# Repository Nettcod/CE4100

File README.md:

# CE4100
Custom USB macro keypad for CE4100

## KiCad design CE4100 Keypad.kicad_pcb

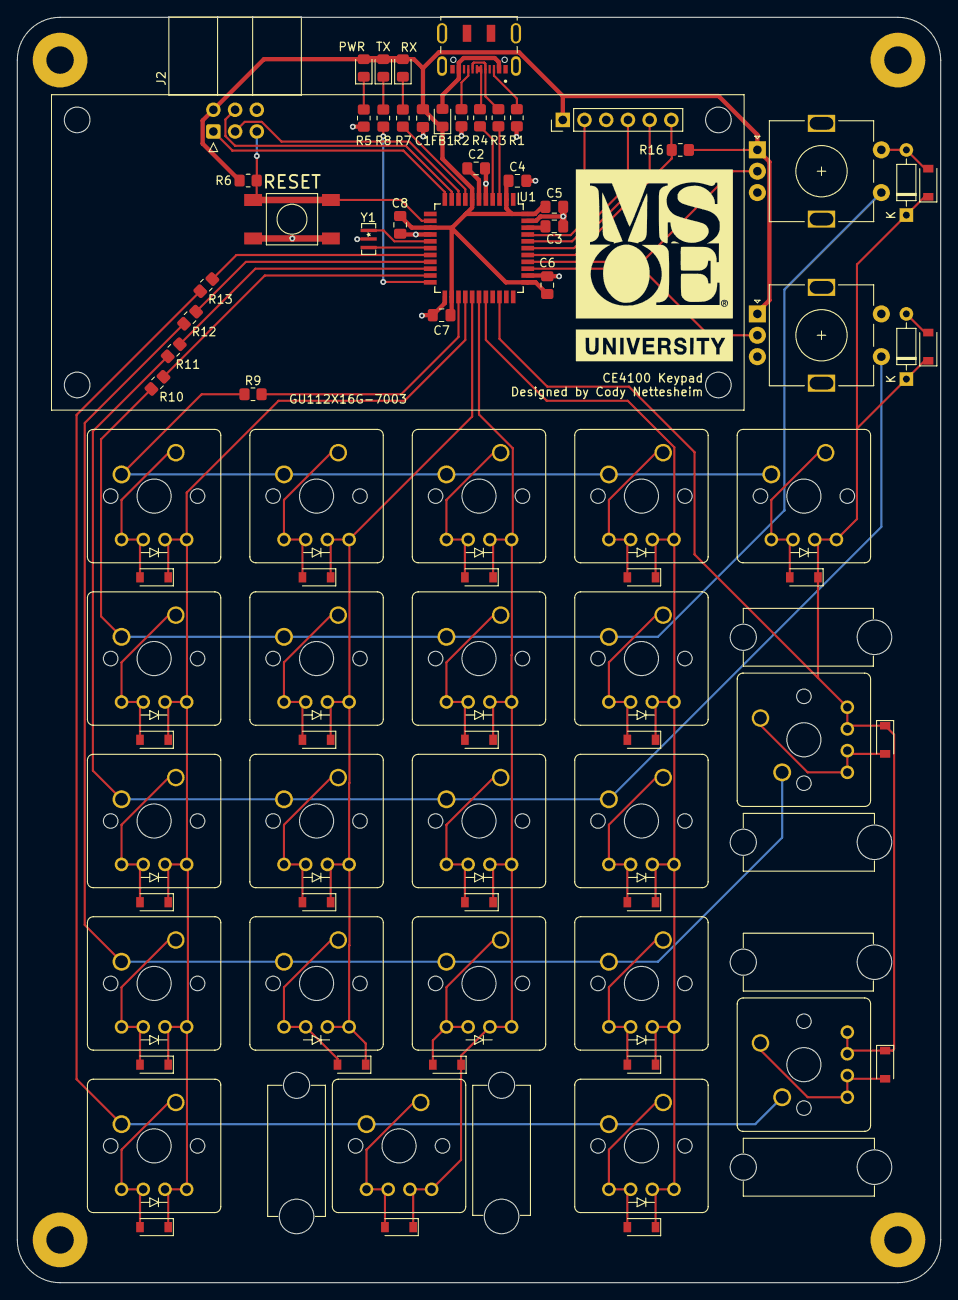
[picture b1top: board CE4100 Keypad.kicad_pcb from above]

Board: 2 copper layers, 108.0 x 148.0 mm, 87 parts (0 on the bottom side), 67 nets.

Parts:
C1: 10uF; C_0805_2012Metric_Pad1.18x1.45mm_HandSolder
C2: 1uF; C_0805_2012Metric_Pad1.18x1.45mm_HandSolder
C3, C4, C5, C6, C7, C8: 100nF; C_0805_2012Metric_Pad1.18x1.45mm_HandSolder
D1: PWR; LED_0805_2012Metric_Pad1.15x1.40mm_HandSolder
D2: RX; LED_0805_2012Metric_Pad1.15x1.40mm_HandSolder
D3: TX; LED_0805_2012Metric_Pad1.15x1.40mm_HandSolder
D4, D5, D6, D7, D8, D9, D10, D11, D12, D13, D14, D15, D16, D17, D18, D19, D20, D21, D22, D23, D24, D25, D27, D29: 1N4148_SMD; D_SOD-123
D26, D28: 1N4148_THT; D_DO-35_SOD27_P7.62mm_Horizontal
FB1: 500mA; D_0805_2012Metric_Pad1.15x1.40mm_HandSolder
G1: LOGO; MSOE
H1, H2, H3, H4: MountingHole; MountingHole_3.2mm_M3_Pad
J1: USB_C; DX07S016JA1R1500
J2: AVR-ISP; IDC-Header_2x03_P2.54mm_Horizontal
J3: GU112X16G-7003
R1, R2: 5.1K; R_0805_2012Metric_Pad1.20x1.40mm_HandSolder
R3, R4: 22; R_0805_2012Metric_Pad1.20x1.40mm_HandSolder
R5, R7, R8, R9, R10, R11, R12, R13: 330; R_0805_2012Metric_Pad1.20x1.40mm_HandSolder
R6, R16: 10K; R_0805_2012Metric_Pad1.20x1.40mm_HandSolder
SW1: RESET; FSM2JSMAA
SW2: Key_M1; Cherry_MX_Diode
SW3: Key_M2; Cherry_MX_Diode
SW4: Key_M3; Cherry_MX_Diode
SW5: Key_M4; Cherry_MX_Diode
SW6: Key_M5; Cherry_MX_Diode
SW7: Key_NumLock; Cherry_MX_Diode
SW8: Key_7; Cherry_MX_Diode
SW9: Key_4; Cherry_MX_Diode
SW10: Key_1; Cherry_MX_Diode
SW11: Key_0; Cherry_MX_Diode_1x2
SW12: Key_Slash; Cherry_MX_Diode
SW13: Key_8; Cherry_MX_Diode
SW14: Key_5; Cherry_MX_Diode
SW15: Key_2; Cherry_MX_Diode
SW16: Key_Star; Cherry_MX_Diode
SW17: Key_9; Cherry_MX_Diode
SW18: Key_6; Cherry_MX_Diode
SW19: Key_3; Cherry_MX_Diode
SW20: Key_Del; Cherry_MX_Diode
SW21: Key_Minus; Cherry_MX_Diode
SW22: Key_Plus; Cherry_MX_Diode_1x2
SW23: Key_Return; Cherry_MX_Diode_1x2
SW24, SW25: Rotary_Switch; RotaryEncoder_Alps_EC11E-Switch_Vertical_H20mm
U1: ATmega32U4; TQFP-44_10x10mm_P0.8mm
Y1: 16MHz; CSTNE_Resonator

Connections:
+5V: C1.1, C4.1, C5.1, C6.1, C7.1, C8.1, D1.2, D2.2, D3.2, FB1.1, J2.2, J3.1, R6.1, R16.1, SW24.A, SW25.A, U1.2, U1.7, U1.14, U1.24, U1.34, U1.44
/COL0: D4.1, D5.1, D6.1, D7.1, D8.1, SW2.4, SW3.4, SW4.4, SW5.4, SW6.4, U1.26
/COL1: D9.1, D10.1, D11.1, D12.1, SW7.4, SW8.4, SW9.4, SW10.4, U1.27
/COL2: D13.1, D14.1, D15.1, D16.1, D17.1, SW11.4, SW12.4, SW13.4, SW14.4, SW15.4, U1.28
/COL3: D18.1, D19.1, D20.1, D21.1, D22.1, SW16.4, SW17.4, SW18.4, SW19.4, SW20.4, U1.29
/COL4: D23.1, D24.1, D25.1, D26.1, D27.1, D28.1, D29.1, SW21.4, SW22.4, SW23.4, U1.31
/D+: R4.1, U1.4
/D-: R3.1, U1.3
/KNOB1: SW24.C, U1.37
/KNOB2: SW25.C, U1.36
/MISO: J2.1, U1.11
/MOSI: J2.4, U1.10
/ROW0: R9.2, U1.25
/ROW1: R10.2, U1.21
/ROW2: R11.2, U1.20
/ROW3: R12.2, U1.19
/ROW4: R13.2, U1.18
/SCK: J2.3, U1.9
/VFD_SBUSY: J3.4, U1.40
/VFD_SCK: J3.5, U1.39
/VFD_SIN: J3.2, U1.41
/VFD_~RST: J3.6, R16.2, U1.38
/~RESET: J2.5, R6.2, SW1.2, U1.13
GND: C1.2, C2.2, C3.2, C4.2, C5.2, C6.2, C7.2, C8.2, H1.1, H2.1, H3.1, H4.1, J1.A1, J1.A12, J1.B1, J1.B12, J1.S1, J2.6, J3.3, R1.1, R2.1, R5.2, SW1.1, SW24.B, SW25.B, U1.5, U1.15, U1.23, U1.35, U1.43, Y1.2
unnamed: C2.1, U1.6
unnamed: C3.1, U1.42
unnamed: D1.1, R5.1
unnamed: D2.1, R7.1
unnamed: D3.1, R8.1
unnamed: D4.2, SW2.2, SW2.3
unnamed: D5.2, SW3.2, SW3.3
unnamed: D6.2, SW4.2, SW4.3
unnamed: D7.2, SW5.2, SW5.3
unnamed: D8.2, SW6.2, SW6.3
unnamed: D9.2, SW7.2, SW7.3
unnamed: D10.2, SW8.2, SW8.3
unnamed: D11.2, SW9.2, SW9.3
unnamed: D12.2, SW10.2, SW10.3
unnamed: D13.2, SW12.2, SW12.3
unnamed: D14.2, SW13.2, SW13.3
unnamed: D15.2, SW14.2, SW14.3
unnamed: D16.2, SW15.2, SW15.3
unnamed: D17.2, SW11.2, SW11.3
unnamed: D18.2, SW16.2, SW16.3
unnamed: D19.2, SW17.2, SW17.3
unnamed: D20.2, SW18.2, SW18.3
unnamed: D21.2, SW19.2, SW19.3
unnamed: D22.2, SW20.2, SW20.3
unnamed: D23.2, SW21.2, SW21.3
unnamed: D24.2, SW22.2, SW22.3
unnamed: D25.2, SW23.2, SW23.3
unnamed: D26.2, D27.2, SW24.S2
unnamed: D28.2, D29.2, SW25.S2
unnamed: FB1.2, J1.A4, J1.A9, J1.B4, J1.B9
unnamed: J1.A5, R1.2
unnamed: J1.A6, J1.B6, R4.2
unnamed: J1.A7, J1.B7, R3.2
unnamed: J1.B5, R2.2
unnamed: R7.2, U1.8
unnamed: R8.2, U1.22
unnamed: R9.1, SW2.1, SW7.1, SW12.1, SW16.1, SW21.1
unnamed: R10.1, SW3.1, SW8.1, SW13.1, SW17.1, SW24.S1
unnamed: R11.1, SW4.1, SW9.1, SW14.1, SW18.1, SW25.S1
unnamed: R12.1, SW5.1, SW10.1, SW15.1, SW19.1, SW22.1
unnamed: R13.1, SW6.1, SW11.1, SW20.1, SW23.1
unnamed: U1.16, Y1.1
unnamed: U1.17, Y1.3

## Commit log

2021-10-15 Added more 3D models and worked on layout
2021-10-19 Added resonator footprint and continued work on layout new file: CSTNE.pretty/CSTNE Resonator.step new file: CSTNE.pretty/CSTNE_Resonator.kicad_mod modified: CE4100 Keypad.kicad_pcb modified: CE4100 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
2021-10-20 Switched to SMD diodes new file: FSM2JSMAA.pretty/FSM2JSMAA-3d.step new file: FSM2JSMAA.pretty/FSM2JSMAA.kicad_mod new file: Switch_Cherry.pretty/Cherry_MX.kicad_mod new file: Switch_Cherry.pretty/Ch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
2021-10-25 Finished design and layout
